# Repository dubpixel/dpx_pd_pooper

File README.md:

<!-- Improved compatibility of back to top link: See: https://github.com/othneildrew/Best-README-Template/pull/73 -->

<!--
*** Thanks for checking out the Best-README-Template. If you have a suggestion
*** that would make this better, please fork the repo and create a pull request
*** or simply open an issue with the tag "enhancement".
*** Don't forget to give the project a star!
*** Thanks again! Now go create something AMAZING! :D
*** /// d   u   b   p   i   x   e   l 
*** this has additionally been changed by dubpixel for the dpx_ series of projects
*** search dpx_pd_pooper .. replace COMMAND OPTION F
*** also has added kicad badge
-->

<!-- PROJECT SHIELDS -->
<!--
*** I'm using markdown "reference style" links for readability.
*** Reference links are enclosed in brackets [ ] instead of parentheses ( ).
*** See the bottom of this document for the declaration of the reference variables
*** for contributors-url, forks-url, etc. This is an optional, concise syntax you may use.
*** https://www.markdownguide.org/basic-syntax/#reference-style-links
***
-->
[![Contributors][contributors-shield]][contributors-url]
[![Forks][forks-shield]][forks-url]
[![Stargazers][stars-shield]][stars-url]
[![Issues][issues-shield]][issues-url]
[![CERN-OHL-W][license-shield]][license-url]
[![LinkedIn][linkedin-shield]][linkedin-url]

<!-- PROJECT LOGO -->
<br />
<div align="center">

<h1 align="center">dpx_pd_pooper </h1>
<h3 align="center"><i>pd poops on tap</i></h3>

  <p align="center">
    ...a ch224a usb-c pd trigger board with a jumper voltage selector (9 / 12 / 15 / 20 / 28 V)
    <br />
    <br />
    <br />
    <br />
    <p align="center">
     <a href="https://github.com/dubpixel/dpx_pd_pooper/tree/main/"><strong>Project Here!</strong></a>
     »  
    <a href="https://github.com/dubpixel/dpx_pd_pooper/tree/main/hardware/production_files_RTG"><strong>BOM Here!</strong></a>
     » 
    <a href="https://dubpixel.github.io/dpx_pd_pooper/"><strong>Manual Here!</strong></a>
     » 
    <a href="https://dubpixel.github.io/dpx_pd_pooper/ibom/"><strong>Interactive BOM Here!</strong></a>
    ·
       <br />
    <a href="https://github.com/dubpixel/dpx_pd_pooper/issues/new?labels=bug&template=bug-report---.md">Report Bug</a>
    ·
    <a href="https://github.com/dubpixel/dpx_pd_pooper/issues/new?labels=enhancement&template=feature-request---.md">Request Feature</a>
    </div>
    </p>
</div>
   <br />
    <br />
    <br />
    <br />
<!-- TABLE OF CONTENTS -->
<details>
  <summary>Table of Contents</summary>
  <ol>
    <li>
      <a href="#about-the-project">About The Project</a>
      <ul>
        <li><a href="#built-with">Built With</a></li>
      </ul>
    </li>
    <li>
      <a href="#getting-started">Getting Started</a>
      <ul>
        <li><a href="#prerequisites">Prerequisites</a></li>
        <li><a href="#installation">Installation</a></li>
      </ul>
    </li>
    <li><a href="#usage">Usage</a></li>
    <li><a href="#roadmap">Roadmap</a></li>
    <li><a href="#contributing">Contributing</a></li>
    <li><a href="#license">License</a></li>
    <li><a href="#contact">Contact</a></li>
    <li><a href="#acknowledgments">Acknowledgments</a></li>
  </ol>
</details>
    <br />
<!-- ABOUT THE PROJECT -->
<details>
  <summary><h3>About The Project</h3></summary>
  a small usb-c power delivery (PD) trigger board. plug it into a PD charger, pick a voltage with a jumper, and get that voltage on a screw terminal.
  built to prove the WCH CH224 PD trigger IC for forthcoming dubpixel / TNG ENT INC devices (dpx_faders uses the CH224K version of this circuit).

  * board: 35.0 x 27.3 mm, 2 layer, 4x M3 holes
  * chip: CH224A, resistor-configured (no firmware, no I2C needed)
  * output: 5 V (no shunt) or 9 / 12 / 15 / 20 / 28 V by shunting one column of the VSEL header
  * status: v0d8 (CH224A) sent to production 2026-11-18. untested until the boards arrive.
  * the earlier CH224K board (v0d5, tag `ch224k`) is the tested baseline.

</br>
www.dubpixel.tv  - i@dubpixel.tv
</br>
</details>

v0d8 (CH224A) front render
![FRONT v0d8][product-front-a]

[v0d8 flip video](images/pdpooper_ch224a_flip.mp4)

Previous revision, v0d5 (CH224K, 3-position DIP switch)
![FRONT v0d5][product-front]
![REAR v0d5][product-rear]

iBOM PCB Front (v0d5)
![iBOM Front][product-pcbFront]

iBOM PCB Rear (v0d5)
![iBOM Rear][product-pcbRear]

<p align="right">(<a href="#readme-top">back to top</a>)</p>

### Built With 
* [![KiCad][KiCad.org]][KiCad-url]
<!--
 * [![Next][Next.js]][Next-url]
 * [![React][React.js]][React-url]
 * [![Vue][Vue.js]][Vue-url]
 * [![Angular][Angular.io]][Angular-url]
 * [![Svelte][Svelte.dev]][Svelte-url]
 * [![Laravel][Laravel.com]][Laravel-url]
 * [![Bootstrap][Bootstrap.com]][Bootstrap-url]
 * [![JQuery][JQuery.com]][JQuery-url]
 
-->
<p align="right">(<a href="#readme-top">back to top</a>)</p>

<!-- GETTING STARTED -->
## Getting Started

### Prerequisites

* a USB-C PD charger that offers the voltage you want (28 V needs a 140 W EPR charger)
* a USB-C cable
* a 2x5 header and shunts (J3) and a 5.08 mm terminal block (J2). Both are left unpopulated by the JLC order and hand-fit.
* KiCad 10 if you want to open the project

### Installation

1. Hand-fit J2 (VOUT terminal block) and J3 (VSEL 2x5 header).
2. Put one shunt on the column for the voltage you want.
3. Plug in the charger, then measure the output at J2 before connecting a load.

<!-- USAGE EXAMPLES -->
## Usage

VSEL (J3) is a 2x5 header. Shunt ONE column. Left to right on the front silk:

| column | voltage | CFG1 resistor |
|---|---|---|
| none | 5 V | none |
| 1 | 9 V | R7 6.8k |
| 2 | 12 V | R8 24k |
| 3 | 15 V | R9 56k |
| 4 | 20 V | R10 120k |
| 5 | 28 V | R11 210k |

Unplug and replug USB-C after moving the shunt. The chip reads the resistor when it negotiates, not continuously.

* PWR LED lights when VBUS is present.
* VOUT (J2) is the negotiated voltage. The board does no regulation, so the load must accept the voltage you picked.
* first power-up of the CH224A board: start on 15 V and check VHV, VBUS and CFG1 before trusting the other columns. R5 is deliberately 10k.

Full details are in the [manual page](https://dubpixel.github.io/dpx_pd_pooper/) (source in `docs/`).

### Known issues (v0d8)

* back silk text (VSEL instructions) runs past the board edge and overlaps some reference designators. Cosmetic.
* the version stamp still reads v0d8 and does not distinguish the CH224A board from the planned next spin.
* CH224A VBUS pin tolerance is contradictory in the WCH datasheet (3.8 V in section 7.1, 32 V in the abs-max table). The 10k at R5 is a first-power-up safety choice.

<p align="right">(<a href="#readme-top">back to top</a>)</p>

<!-- ROADMAP -->
## Roadmap

- [x] v0d5: CH224K board with 3-position DIP switch (tag `ch224k`)
- [x] v0d8: CH224A with VSEL jumper header, 9 / 12 / 15 / 20 / 28 V (sent to production 2026-11-18)
- [ ] bench-test the CH224A board against the CH224K board, same charger
- [ ] fix the back silk overflow and bump the version stamp
- [ ] decide whether the CH224A goes into dpx_faders rev 0.8
- [ ] LCSC part numbers for J2 and J3 so JLC can place them

See the [open issues](https://github.com/dubpixel/dpx_pd_pooper/issues) for a full list of proposed features (and known issues).

<p align="right">(<a href="#readme-top">back to top</a>)</p>

<!-- CONTRIBUTING -->
## Contributing

Contributions are what make the open source community such an amazing place to learn, inspire, and create. Any contributions you make are **greatly appreciated**.

If you have a suggestion that would make this better, please fork the repo and create a pull request. You can also simply open an issue with the tag "enhancement".
Don't forget to give the project a star! Thanks again!

1. Fork the Project
2. Create your Feature Branch (`git checkout -b feature/AmazingFeature`)
3. Commit your Changes (`git commit -m 'Add some AmazingFeature'`)
4. Push to the Branch (`git push origin feature/AmazingFeature`)
5. Open a Pull Request

<p align="right">(<a href="#readme-top">back to top</a>)</p>

### Top contributors:

<!-- LICENSE -->
## License

Distributed under the CERN Open Hardware Licence Version 2 - Weakly Reciprocal (CERN-OHL-W-2.0). See `license.txt` for more information.

<p align="right">(<a href="#readme-top">back to top</a>)</p>

<!-- CONTACT -->
## Contact

#Joshua Fleitell - i@dubpixel.tv

Project Link: [https://github.com/dubpixel/dpx_pd_pooper](https://github.com/dubpixel/dpx_pd_pooper)

<p align="right">(<a href="#readme-top">back to top</a>)</p>

<!-- ACKNOWLEDGMENTS -->
## Acknowledgments

* WCH CH224A / CH224K datasheets
* [Best-README-Template](https://github.com/othneildrew/Best-README-Template)

<p align="right">(<a href="#readme-top">back to top</a>)</p>

<!-- MARKDOWN LINKS & IMAGES -->
<!-- https://www.markdownguide.org/basic-syntax/#reference-style-links -->
[contributors-shield]: https://img.shields.io/github/contributors/dubpixel/dpx_pd_pooper.svg?style=for-the-badge
[contributors-url]: https://github.com/dubpixel/dpx_pd_pooper/graphs/contributors
[forks-shield]: https://img.shields.io/github/forks/dubpixel/dpx_pd_pooper.svg?style=for-the-badge
[forks-url]: https://github.com/dubpixel/dpx_pd_pooper/network/members
[stars-shield]: https://img.shields.io/github/stars/dubpixel/dpx_pd_pooper.svg?style=for-the-badge
[stars-url]: https://github.com/dubpixel/dpx_pd_pooper/stargazers
[issues-shield]: https://img.shields.io/github/issues/dubpixel/dpx_pd_pooper.svg?style=for-the-badge
[issues-url]: https://github.com/dubpixel/dpx_pd_pooper/issues
[license-shield]: https://img.shields.io/badge/license-CERN--OHL--W--2.0-blue?style=for-the-badge
[license-url]: https://github.com/dubpixel/dpx_pd_pooper/blob/main/license.txt
[linkedin-shield]: https://img.shields.io/badge/-LinkedIn-black.svg?style=for-the-badge&logo=linkedin&colorB=555
[linkedin-url]: https://linkedin.com/in/jfleitell
[product-screenshot]: images/screenshot.png
[product-front-a]: images/pdpooper_ch224a_front.png
[product-front]: images/front.png
[product-rear]: images/rear.png
[product-pcbFront]: images/pcb_front.png
[product-pcbRear]: images/pcb_rear.png
[Next.js]: https://img.shields.io/badge/next.js-000000?style=for-the-badge&logo=nextdotjs&logoColor=white
[Next-url]: https://nextjs.org/
[React.js]: https://img.shields.io/badge/React-20232A?style=for-the-badge&logo=react&logoColor=61DAFB
[React-url]: https://reactjs.org/
[Vue.js]: https://img.shields.io/badge/Vue.js-35495E?style=for-the-badge&logo=vuedotjs&logoColor=4FC08D
[Vue-url]: https://vuejs.org/
[Angular.io]: https://img.shields.io/badge/Angular-DD0031?style=for-the-badge&logo=angular&logoColor=white
[Angular-url]: https://angular.io/
[Svelte.dev]: https://img.shields.io/badge/Svelte-4A4A55?style=for-the-badge&logo=svelte&logoColor=FF3E00
[Svelte-url]: https://svelte.dev/
[Laravel.com]: https://img.shields.io/badge/Laravel-FF2D20?style=for-the-badge&logo=laravel&logoColor=white
[Laravel-url]: https://laravel.com
[Bootstrap.com]: https://img.shields.io/badge/Bootstrap-563D7C?style=for-the-badge&logo=bootstrap&logoColor=white
[Bootstrap-url]: https://getbootstrap.com
[JQuery.com]: https://img.shields.io/badge/jQuery-0769AD?style=for-the-badge&logo=jquery&logoColor=white
[JQuery-url]: https://jquery.com 
[KiCad.org]: https://img.shields.io/badge/KiCad-v10-blue
[KiCad-url]: https://kicad.org

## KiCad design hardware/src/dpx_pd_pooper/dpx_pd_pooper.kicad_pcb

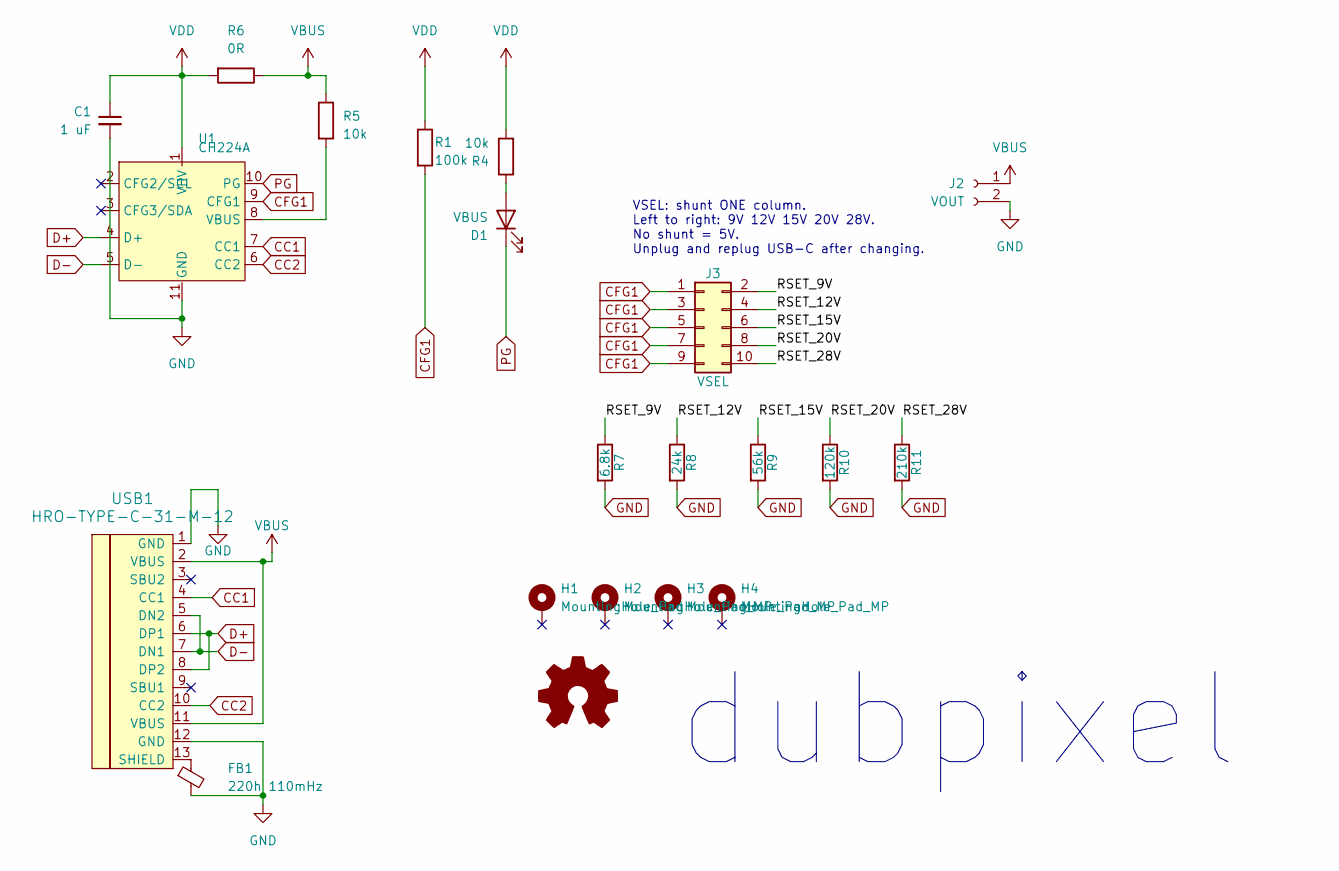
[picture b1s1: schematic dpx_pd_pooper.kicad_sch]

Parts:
C1: 1 uF; C_0603_1608Metric_Pad1.08x0.95mm_HandSolder; LCSC C15849
D1: VBUS; LED_0805_2012Metric_Pad1.15x1.40mm_HandSolder; LCSC C2297
FB1: 220h 110mHz; FERRITE_0603; LCSC C80165
H1: MountingHole_Pad; MountingHole_2.2mm_M2_ISO7380_Pad_TopBottom
H2, H3, H4: MountingHole_Pad_MP; MountingHole_2.2mm_M2_ISO7380_Pad_TopBottom
J2: VOUT; TerminalBlock_Phoenix_MKDS-1,5-2-5.08_1x02_P5.08mm_Horizont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
J3: VSEL; PinHeader_2x05_P2.54mm_Vertical
R1: 100k; R_0805_2012Metric_Pad1.20x1.40mm_HandSolder; LCSC C149504
R4, R5: 10k; R_0805_2012Metric_Pad1.20x1.40mm_HandSolder; LCSC C17414
R6: 0R; R_0805_2012Metric_Pad1.20x1.40mm_HandSolder; LCSC C17477
R7: 6.8k; R_0805_2012Metric_Pad1.20x1.40mm_HandSolder; LCSC C17772
R8: 24k; R_0805_2012Metric_Pad1.20x1.40mm_HandSolder; LCSC C17575
R9: 56k; R_0805_2012Metric_Pad1.20x1.40mm_HandSolder; LCSC C17756
R10: 120k; R_0805_2012Metric_Pad1.20x1.40mm_HandSolder; LCSC C17436
R11: 210k; R_0805_2012Metric_Pad1.20x1.40mm_HandSolder; LCSC C17547
SYM1: Logo_Open_Hardware_Small; OSHW-LogoNT_7.3x6mm_Silk
U1: CH224A; SSOP-10-1EP_3.9x4.9mm_P1mm_EP2.1x3.3mm_ThermalVias; LCSC C42459160
USB1: HRO-TYPE-C-31-M-12; HRO-TYPE-C-31-M-12-Assembly; LCSC C165948

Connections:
/RSET_9V: J3.2, R7.1
/RSET_12V: J3.4, R8.1
/RSET_15V: J3.6, R9.1
/RSET_20V: J3.8, R10.1
/RSET_28V: J3.10, R11.1
CC1: U1.7 (CC1), USB1.4 (CC1)
CC2: U1.6 (CC2), USB1.10 (CC2)
CFG1: J3.1, J3.3, J3.5, J3.7, J3.9, R1.2, U1.9 (CFG1)
D+: U1.4 (D+), USB1.6 (DP1), USB1.8 (DP2)
D-: U1.5 (D-), USB1.5 (DN2), USB1.7 (DN1)
GND: C1.2, FB1.2, J2.2, R7.2, R8.2, R9.2, R10.2, R11.2, U1.11 (GND), USB1.1 (GND), USB1.12 (GND)
unnamed 11: D1.2 (A), R4.1; also elsewhere on the board
unnamed: R5.2, U1.8 (VBUS)
unnamed: FB1.1, USB1.13 (SHIELD)
PG: D1.1 (K), U1.10 (PG); also elsewhere on the board
VBUS: J2.1, R5.1, R6.1, USB1.2 (VBUS), USB1.11 (VBUS)
VDD: C1.1, R1.1, R4.2, R6.2, U1.1 (VHV)

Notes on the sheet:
VSEL: shunt ONE column. Left to right: 9V 12V 15V 20V 28V. No shunt = 5V. Unplug and replug USB-C after changing.
dubpixel

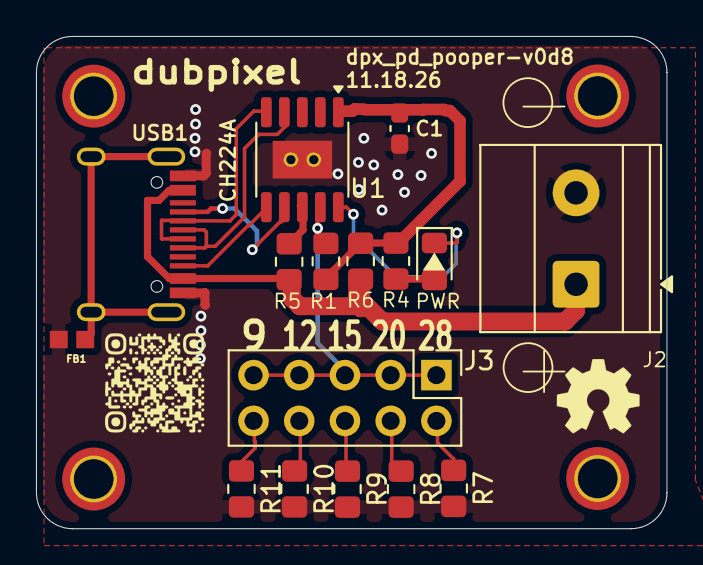
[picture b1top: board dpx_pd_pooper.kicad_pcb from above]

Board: 2 copper layers, 35.0 x 27.3 mm, 21 parts (0 on the bottom side), 17 nets.

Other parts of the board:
PWR: VBUS; LED_0805_2012Metric_Pad1.15x1.40mm_HandSolder

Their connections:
unnamed 11: PWR.2 (A); also elsewhere on the board
PG: PWR.1 (K); also elsewhere on the board

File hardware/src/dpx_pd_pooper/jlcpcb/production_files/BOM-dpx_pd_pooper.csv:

Comment,Designator,Footprint,LCSC,Quantity
0R,R6,R_0805_2012Metric_Pad1.20x1.40mm_HandSolder,C17477,1
1 uF,C1,C_0603_1608Metric_Pad1.08x0.95mm_HandSolder,C15849,1
100k,R1,R_0805_2012Metric_Pad1.20x1.40mm_HandSolder,C149504,1
10k,"R4,R5",R_0805_2012Metric_Pad1.20x1.40mm_HandSolder,C17414,2
120k,R10,R_0805_2012Metric_Pad1.20x1.40mm_HandSolder,C17436,1
210k,R11,R_0805_2012Metric_Pad1.20x1.40mm_HandSolder,C17547,1
220h 110mHz,FB1,FERRITE_0603,C80165,1
24k,R8,R_0805_2012Metric_Pad1.20x1.40mm_HandSolder,C17575,1
56k,R9,R_0805_2012Metric_Pad1.20x1.40mm_HandSolder,C17756,1
6.8k,R7,R_0805_2012Metric_Pad1.20x1.40mm_HandSolder,C17772,1
CH224A,U1,SSOP-10-1EP_3.9x4.9mm_P1mm_EP2.1x3.3mm_ThermalVias,C42459160,1
HRO-TYPE-C-31-M-12,USB1,HRO-TYPE-C-31-M-12-Assembly,C165948,1
VBUS,PWR,LED_0805_2012Metric_Pad1.15x1.40mm_HandSolder,C2297,1
VOUT,J2,"TerminalBlock_Phoenix_MKDS-1,5-2-5.08_1x02_P5.08mm_Horizontal",,1
VSEL,J3,PinHeader_2x05_P2.54mm_Vertical,,1

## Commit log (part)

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2024-12-08 Update README.md
    whoops~
2024-12-08 Update README.md
    again...
2024-12-09 Update README.md
    more dumb mistakes in the template
2024-12-09 ibom and images
    update ibom and product images
2024-12-15 updated production files
    qr code and some fixes
2024-12-15 lol missing the CH224K ?
